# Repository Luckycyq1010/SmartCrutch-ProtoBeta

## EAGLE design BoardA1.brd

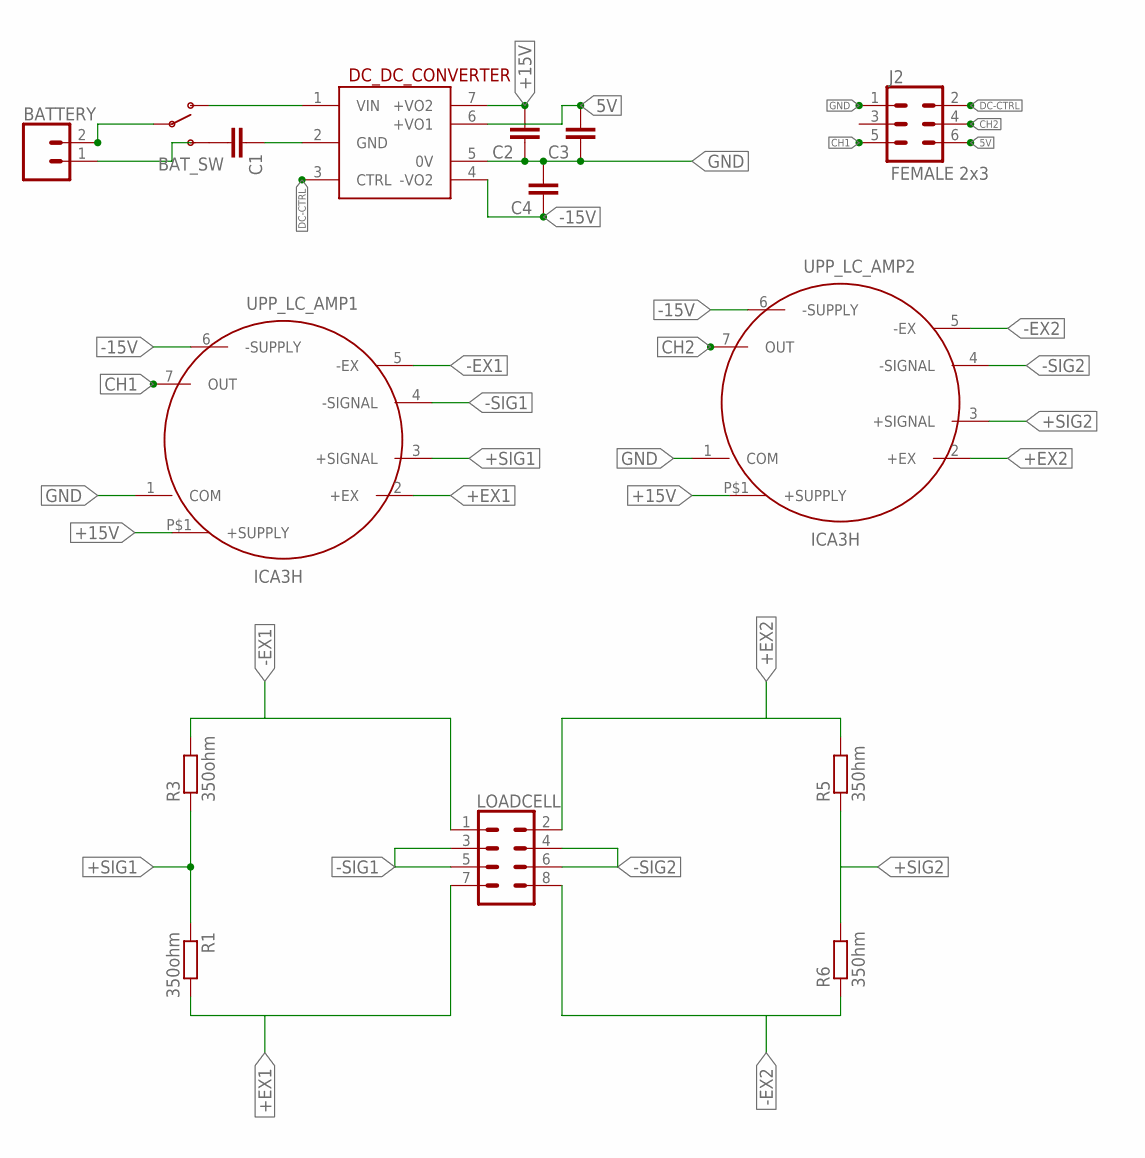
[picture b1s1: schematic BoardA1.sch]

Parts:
BATTERY: CONN_02; 1X02
BAT_SW: SWITCH-SPDTPTH; SWITCH-SPDT
C1, C2, C3, C4: C2.5/2; C2.5-2
DC_DC_CONVERTER: DC-DC; DC-DCCONVERTER
J2: FEMALE 2x3; 2X3
LOADCELL: CONN_04X2; 2X4
R1, R3: 350ohm; 0207/10
R5, R6: 350hm; 0207/10
UPP_LC_AMP1, UPP_LC_AMP2: ICA3H

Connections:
5V: C3.2, DC_DC_CONVERTER.6 (+VO1), J2.6
+15V: C2.2, DC_DC_CONVERTER.7 (+VO2), UPP_LC_AMP1.P$1 (+SUPPLY), UPP_LC_AMP2.P$1 (+SUPPLY)
+EX1: LOADCELL.7, R1.2, UPP_LC_AMP1.2 (+EX)
+EX2: LOADCELL.2, R5.2, UPP_LC_AMP2.2 (+EX)
+SIG1: R1.1, R3.1, UPP_LC_AMP1.3 (+SIGNAL)
+SIG2: R5.1, R6.2, UPP_LC_AMP2.3 (+SIGNAL)
-15V: C4.1, DC_DC_CONVERTER.4 (-VO2), UPP_LC_AMP1.6 (-SUPPLY), UPP_LC_AMP2.6 (-SUPPLY)
-EX1: LOADCELL.1, R3.2, UPP_LC_AMP1.5 (-EX)
-EX2: LOADCELL.8, R6.1, UPP_LC_AMP2.5 (-EX)
-SIG1: LOADCELL.3, LOADCELL.5, UPP_LC_AMP1.4 (-SIGNAL)
-SIG2: LOADCELL.4, LOADCELL.6, UPP_LC_AMP2.4 (-SIGNAL)
CH1: J2.5, UPP_LC_AMP1.7 (OUT)
CH2: J2.4, UPP_LC_AMP2.7 (OUT)
DC-CTRL: DC_DC_CONVERTER.3 (CTRL), J2.2
GND: C2.1, C3.1, C4.2, DC_DC_CONVERTER.5 (0V), J2.1, UPP_LC_AMP1.1 (COM), UPP_LC_AMP2.1 (COM)
unnamed: C1.1, DC_DC_CONVERTER.2 (GND)
unnamed: BAT_SW.1 (O), DC_DC_CONVERTER.1 (VIN)
unnamed: BATTERY.2, BAT_SW.2

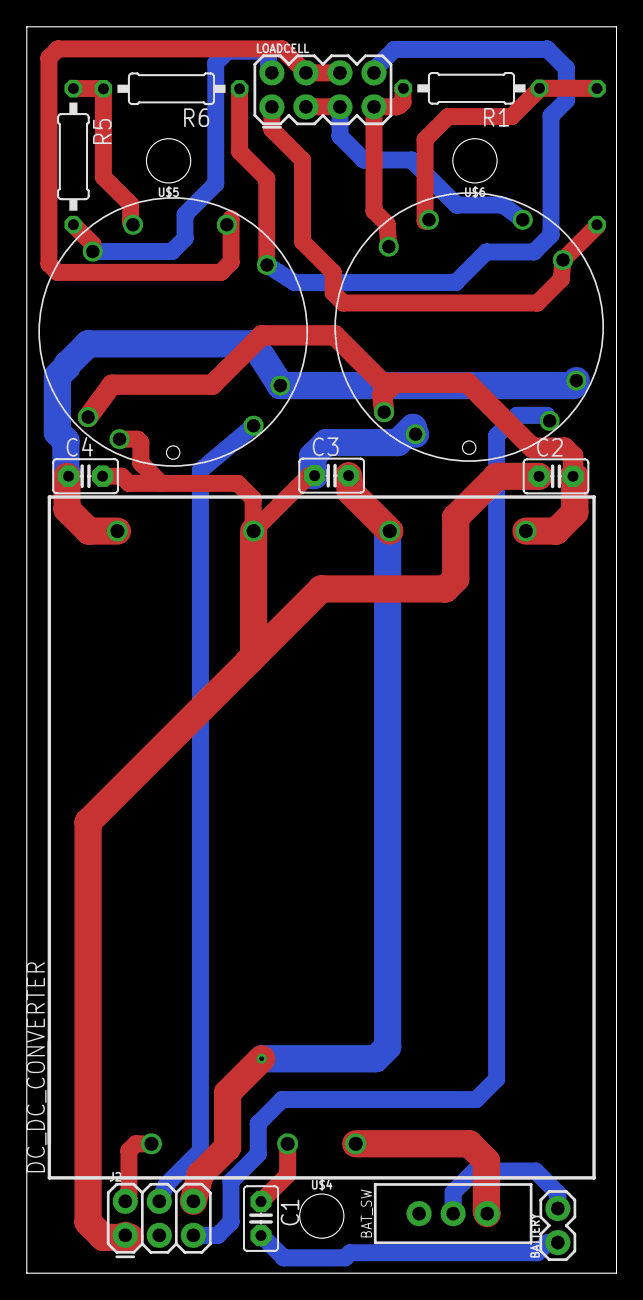
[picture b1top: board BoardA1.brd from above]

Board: 2 copper layers, 44.0 x 93.0 mm, 18 parts (1 on the bottom side), 18 nets.

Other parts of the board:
U$4, U$5, U$6: STAND-OFF

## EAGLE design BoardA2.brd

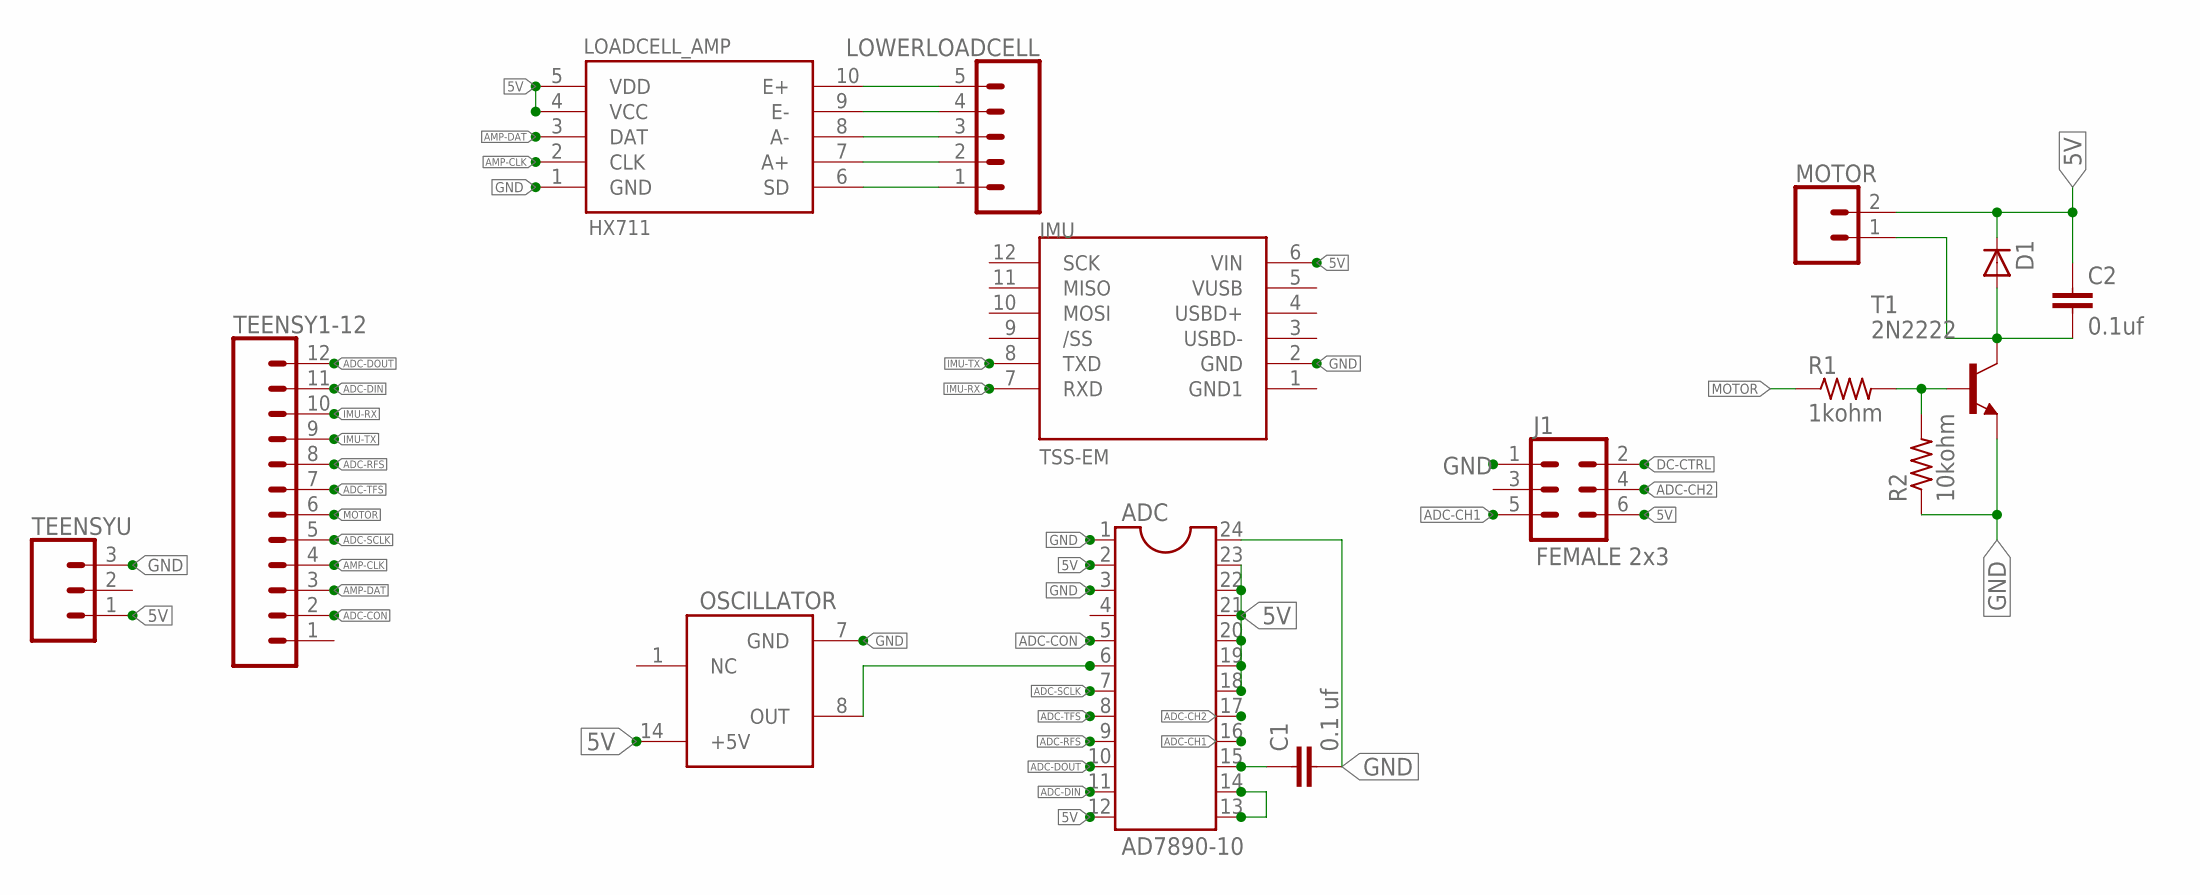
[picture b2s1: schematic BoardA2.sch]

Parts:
ADC: AD7890-10; DIL24-3
C1: 0.1 uf; C5B2.5
C2: 0.1uf; C5B2.5
D1: DIODE_E-DO35-7; DIODE_DO35-7
IMU: TSS-EM; IMU
J1: FEMALE 2x3; 2X3
LOADCELL_AMP: HX711; LOADCELLAMP2
LOWERLOADCELL: CONN_05; 1X05
MOTOR: CONN_02; 1X02
OSCILLATOR: CLOCK-ECS-100X; ECS-100X
R1: 1kohm; 0204/5
R2: 10kohm; 0204/5
T1: 2N2222; TO18
TEENSY1-12: CONN_12; 1X12
TEENSYU: CONN_03; 1X03

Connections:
5V: ADC.2, ADC.12, ADC.18, ADC.19, ADC.20, ADC.21, ADC.22, ADC.23, C2.1, D1.C (A), IMU.6 (VIN), J1.6, LOADCELL_AMP.4 (VCC), LOADCELL_AMP.5 (VDD), MOTOR.2, OSCILLATOR.14 (+5V), TEENSYU.1
ADC-CH1: ADC.16, J1.5
ADC-CH2: ADC.17, J1.4
ADC-CLK: ADC.6, OSCILLATOR.8 (OUT)
ADC-CON: ADC.5, TEENSY1-12.2
ADC-DIN: ADC.11, TEENSY1-12.11
ADC-DOUT: ADC.10, TEENSY1-12.12
ADC-RFS: ADC.9, TEENSY1-12.8
ADC-SCLK: ADC.7, TEENSY1-12.5
ADC-TFS: ADC.8, TEENSY1-12.7
AMP-A+: LOADCELL_AMP.7 (A+), LOWERLOADCELL.2
AMP-A-: LOADCELL_AMP.8 (A-), LOWERLOADCELL.3
AMP-CLK: LOADCELL_AMP.2 (CLK), TEENSY1-12.4
AMP-DAT: LOADCELL_AMP.3 (DAT), TEENSY1-12.3
AMP-E+: LOADCELL_AMP.10 (E+), LOWERLOADCELL.5
AMP-E-: LOADCELL_AMP.9 (E-), LOWERLOADCELL.4
AMP-SD: LOADCELL_AMP.6 (SD), LOWERLOADCELL.1
DC-CTRL: J1.2
GND: ADC.1, ADC.3, ADC.24, C1.2, IMU.2 (GND), J1.1, LOADCELL_AMP.1 (GND), OSCILLATOR.7 (GND), R2.1, T1.1 (E), TEENSYU.3
IMU-RX: IMU.7 (RXD), TEENSY1-12.10
IMU-TX: IMU.8 (TXD), TEENSY1-12.9
MOTOR: R1.1, TEENSY1-12.6
unnamed: ADC.13, ADC.14
unnamed: ADC.15, C1.1
unnamed: C2.2, D1.A (C), MOTOR.1, T1.3 (C)
unnamed: R1.2, R2.2, T1.2 (B)

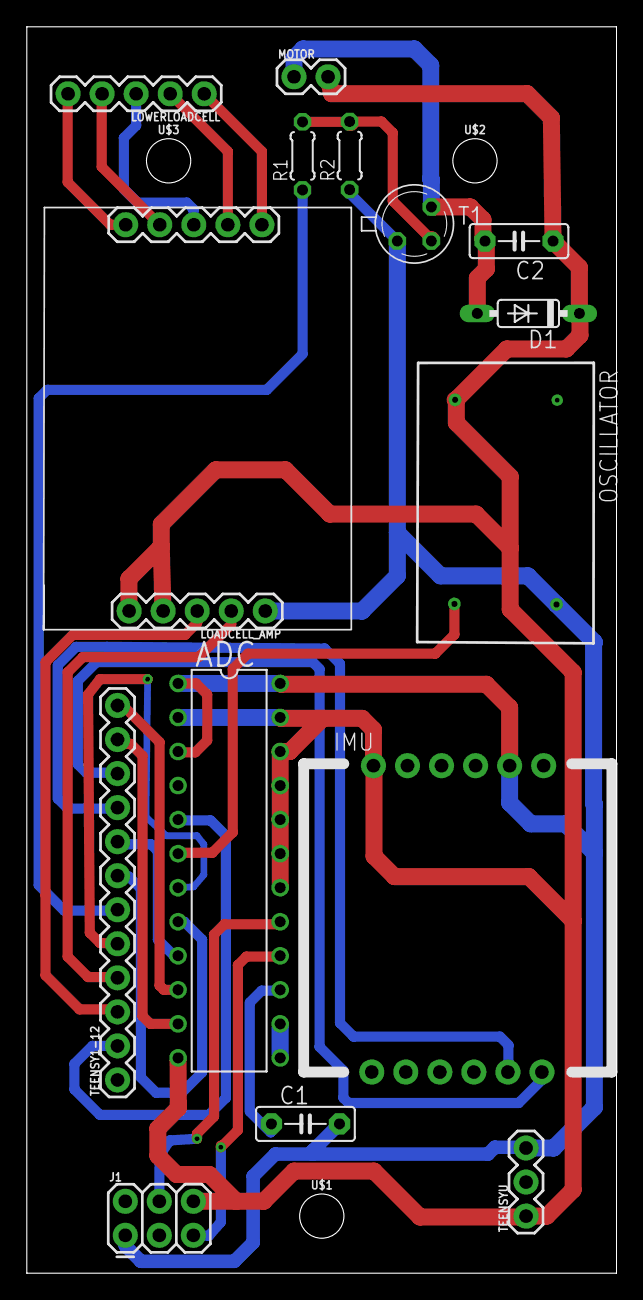
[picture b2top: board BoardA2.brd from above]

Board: 2 copper layers, 44.0 x 93.0 mm, 18 parts (0 on the bottom side), 25 nets.

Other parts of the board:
U$1, U$2, U$3: STAND-OFF

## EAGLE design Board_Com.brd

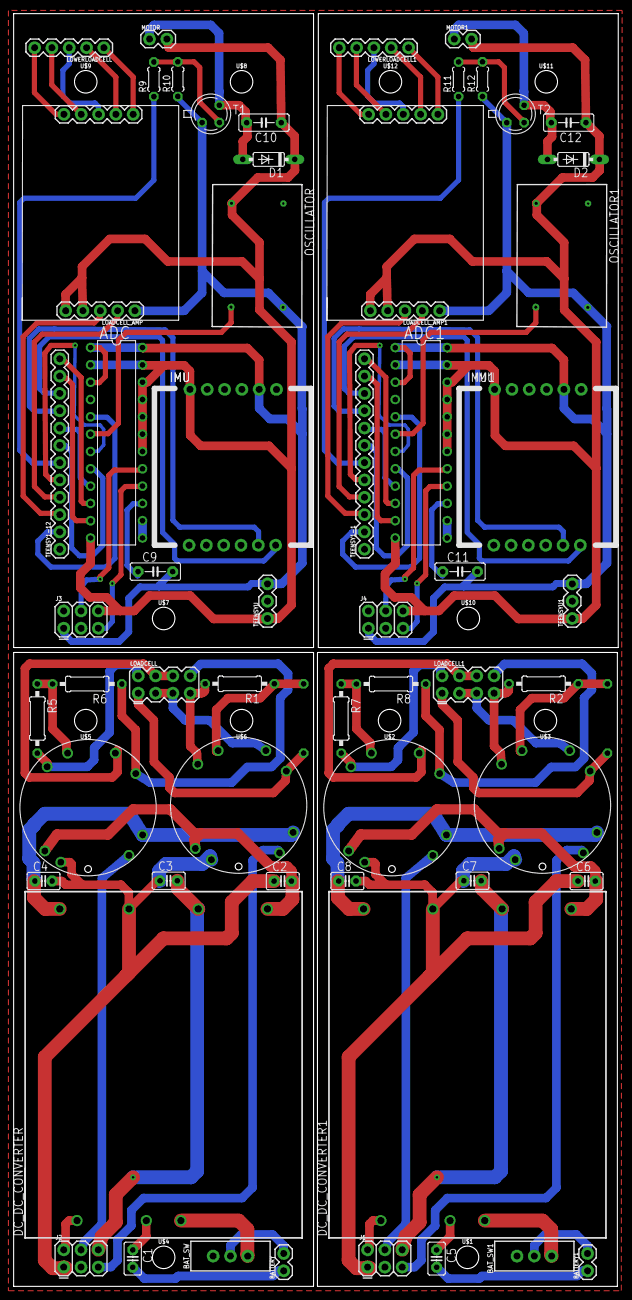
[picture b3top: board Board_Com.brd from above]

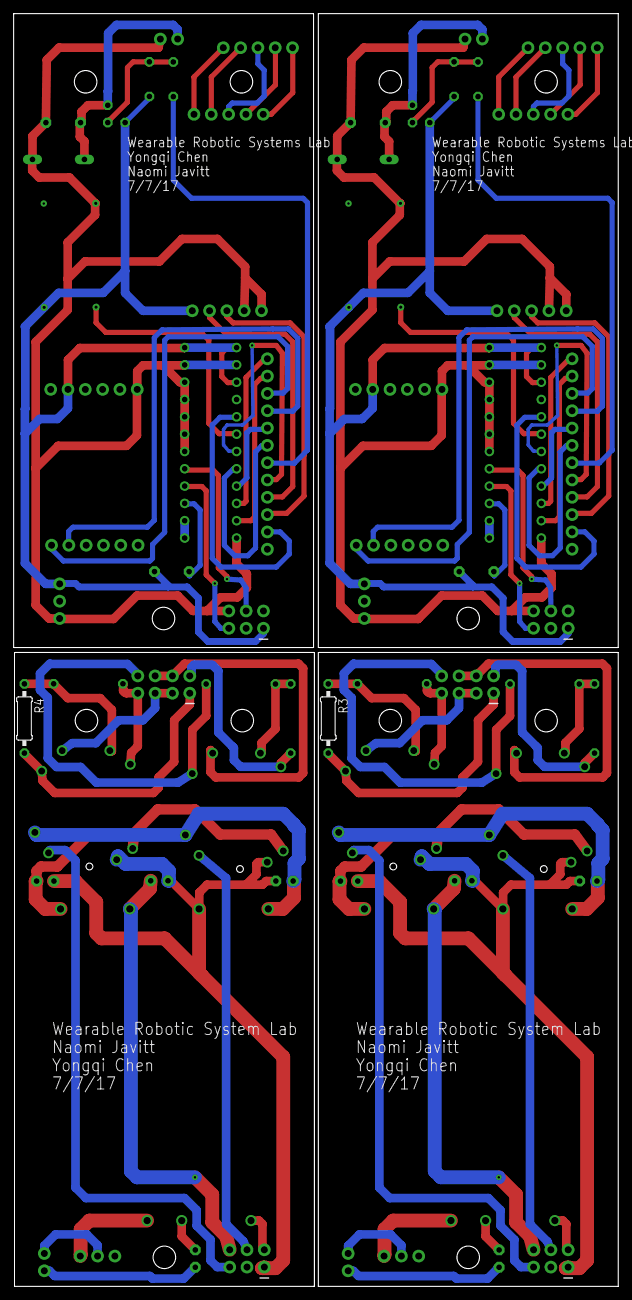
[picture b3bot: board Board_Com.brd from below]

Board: 2 copper layers, 88.7 x 186.7 mm, 72 parts (2 on the bottom side), 86 nets.

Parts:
ADC, ADC1: AD7890-10; DIL24-3
BATTERY, BATTERY1: 1X02
BAT_SW, BAT_SW1: SWITCH-SPDT
C1, C2, C3, C4, C5, C6, C7, C8: C2.5-2
C9, C11: 0.1 uf; C5B2.5
C10, C12: 0.1uf; C5B2.5
D1, D2: DIODE_DO35-7
DC_DC_CONVERTER, DC_DC_CONVERTER1: DC-DCCONVERTER
IMU, IMU1: TSS-EM; IMU
J1, J2, J3, J4: FEMALE 2x3; 2X3
LOADCELL, LOADCELL1: 2X4
LOADCELL_AMP, LOADCELL_AMP1: HX711; LOADCELLAMP2
LOWERLOADCELL, LOWERLOADCELL1: 1X05
MOTOR, MOTOR1: 1X02
OSCILLATOR, OSCILLATOR1: CLOCK-ECS-100X; ECS-100X
R1, R2, R3, R4: 350ohm; 0207/10
R5, R6, R7, R8: 350hm; 0207/10
R9, R11: 1kohm; 0204/5
R10, R12: 10kohm; 0204/5
T1, T2: 2N2222; TO18
TEENSY1-1, TEENSY1-12: 1X12
TEENSYU, TEENSYU1: 1X03
U$1, U$2, U$3, U$4, U$5, U$6, U$7, U$8, U$9, U$10, U$11, U$12: STAND-OFF
UPP_LC_AMP1, UPP_LC_AMP2, UPP_LC_AMP3, UPP_LC_AMP4: ICA3H

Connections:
5V: C3.2, DC_DC_CONVERTER.6, J2.6
5V1: C7.2, DC_DC_CONVERTER1.6, J1.6
5V2: ADC.2, ADC.12, ADC.18, ADC.19, ADC.20, ADC.21, ADC.22, ADC.23, C10.1, D1.C, IMU.6, J3.6, LOADCELL_AMP.4, LOADCELL_AMP.5, MOTOR.2, OSCILLATOR.14, TEENSYU.1
5V3: ADC1.2, ADC1.12, ADC1.18, ADC1.19, ADC1.20, ADC1.21, ADC1.22, ADC1.23, C12.1, D2.C, IMU1.6, J4.6, LOADCELL_AMP1.4, LOADCELL_AMP1.5, MOTOR1.2, OSCILLATOR1.14, TEENSYU1.1
+15V: C2.2, DC_DC_CONVERTER.7, UPP_LC_AMP1.P$1, UPP_LC_AMP2.P$1
+15V1: C6.2, DC_DC_CONVERTER1.7, UPP_LC_AMP3.P$1, UPP_LC_AMP4.P$1
+EX1: LOADCELL.7, R1.2, UPP_LC_AMP1.2
+EX2: LOADCELL.2, R5.2, UPP_LC_AMP2.2
+EX3: LOADCELL1.7, R2.2, UPP_LC_AMP3.2
+EX4: LOADCELL1.2, R7.2, UPP_LC_AMP4.2
+SIG1: R1.1, R3.1, UPP_LC_AMP1.3
+SIG2: R5.1, R6.2, UPP_LC_AMP2.3
+SIG3: R2.1, R4.1, UPP_LC_AMP3.3
+SIG4: R7.1, R8.2, UPP_LC_AMP4.3
-15V: C4.1, DC_DC_CONVERTER.4, UPP_LC_AMP1.6, UPP_LC_AMP2.6
-15V1: C8.1, DC_DC_CONVERTER1.4, UPP_LC_AMP3.6, UPP_LC_AMP4.6
-EX1: LOADCELL.1, R3.2, UPP_LC_AMP1.5
-EX2: LOADCELL.8, R6.1, UPP_LC_AMP2.5
-EX3: LOADCELL1.1, R4.2, UPP_LC_AMP3.5
-EX4: LOADCELL1.8, R8.1, UPP_LC_AMP4.5
-SIG1: LOADCELL.3, LOADCELL.5, UPP_LC_AMP1.4
-SIG2: LOADCELL.4, LOADCELL.6, UPP_LC_AMP2.4
-SIG3: LOADCELL1.3, LOADCELL1.5, UPP_LC_AMP3.4
-SIG4: LOADCELL1.4, LOADCELL1.6, UPP_LC_AMP4.4
ADC-CH1: ADC.16, J3.5
ADC-CH2: ADC.17, J3.4
ADC-CH3: ADC1.16, J4.5
ADC-CH4: ADC1.17, J4.4
ADC-CLK: ADC.6, OSCILLATOR.8
ADC-CLK1: ADC1.6, OSCILLATOR1.8
ADC-CON: ADC.5, TEENSY1-12.2
ADC-CON1: ADC1.5, TEENSY1-1.2
ADC-DIN: ADC.11, TEENSY1-12.11
ADC-DIN1: ADC1.11, TEENSY1-1.11
ADC-DOUT: ADC.10, TEENSY1-12.12
ADC-DOUT1: ADC1.10, TEENSY1-1.12
ADC-RFS: ADC.9, TEENSY1-12.8
ADC-RFS1: ADC1.9, TEENSY1-1.8
ADC-SCLK: ADC.7, TEENSY1-12.5
ADC-SCLK1: ADC1.7, TEENSY1-1.5
ADC-TFS: ADC.8, TEENSY1-12.7
ADC-TFS1: ADC1.8, TEENSY1-1.7
AMP-A+: LOADCELL_AMP.7, LOWERLOADCELL.2
AMP-A+1: LOADCELL_AMP1.7, LOWERLOADCELL1.2
AMP-A-: LOADCELL_AMP.8, LOWERLOADCELL.3
AMP-A-1: LOADCELL_AMP1.8, LOWERLOADCELL1.3
AMP-CLK: LOADCELL_AMP.2, TEENSY1-12.4
AMP-CLK1: LOADCELL_AMP1.2, TEENSY1-1.4
AMP-DAT: LOADCELL_AMP.3, TEENSY1-12.3
AMP-DAT1: LOADCELL_AMP1.3, TEENSY1-1.3
AMP-E+: LOADCELL_AMP.10, LOWERLOADCELL.5
AMP-E+1: LOADCELL_AMP1.10, LOWERLOADCELL1.5
AMP-E-: LOADCELL_AMP.9, LOWERLOADCELL.4
AMP-E-1: LOADCELL_AMP1.9, LOWERLOADCELL1.4
AMP-SD: LOADCELL_AMP.6, LOWERLOADCELL.1
AMP-SD1: LOADCELL_AMP1.6, LOWERLOADCELL1.1
CH1: J2.5, UPP_LC_AMP1.7
CH2: J2.4, UPP_LC_AMP2.7
CH3: J1.5, UPP_LC_AMP3.7
CH4: J1.4, UPP_LC_AMP4.7
DC-CTRL: DC_DC_CONVERTER.3, J2.2
DC-CTRL1: DC_DC_CONVERTER1.3, J1.2
GND: C2.1, C3.1, C4.2, DC_DC_CONVERTER.5, J2.1, UPP_LC_AMP1.1, UPP_LC_AMP2.1
GND1: C6.1, C7.1, C8.2, DC_DC_CONVERTER1.5, J1.1, UPP_LC_AMP3.1, UPP_LC_AMP4.1
GND2: ADC.1, ADC.3, ADC.24, C9.2, IMU.2, J3.1, LOADCELL_AMP.1, OSCILLATOR.7, R10.1, T1.1, TEENSYU.3
GND3: ADC1.1, ADC1.3, ADC1.24, C11.2, IMU1.2, J4.1, LOADCELL_AMP1.1, OSCILLATOR1.7, R12.1, T2.1, TEENSYU1.3
IMU-RX: IMU.7, TEENSY1-12.10
IMU-RX1: IMU1.7, TEENSY1-1.10
IMU-TX: IMU.8, TEENSY1-12.9
IMU-TX1: IMU1.8, TEENSY1-1.9
MOTOR: R9.1, TEENSY1-12.6
MOTOR1: R11.1, TEENSY1-1.6
unnamed: C1.1, DC_DC_CONVERTER.2
unnamed: BAT_SW.1, DC_DC_CONVERTER.1
unnamed: C5.1, DC_DC_CONVERTER1.2
unnamed: BATTERY.2, BAT_SW.2
unnamed: BAT_SW1.1, DC_DC_CONVERTER1.1
unnamed: BATTERY1.2, BAT_SW1.2
unnamed: ADC.13, ADC.14
unnamed: ADC.15, C9.1
unnamed: C10.2, D1.A, MOTOR.1, T1.3
unnamed: R9.2, R10.2, T1.2
unnamed: ADC1.13, ADC1.14
unnamed: ADC1.15, C11.1
unnamed: C12.2, D2.A, MOTOR1.1, T2.3
unnamed: R11.2, R12.2, T2.2

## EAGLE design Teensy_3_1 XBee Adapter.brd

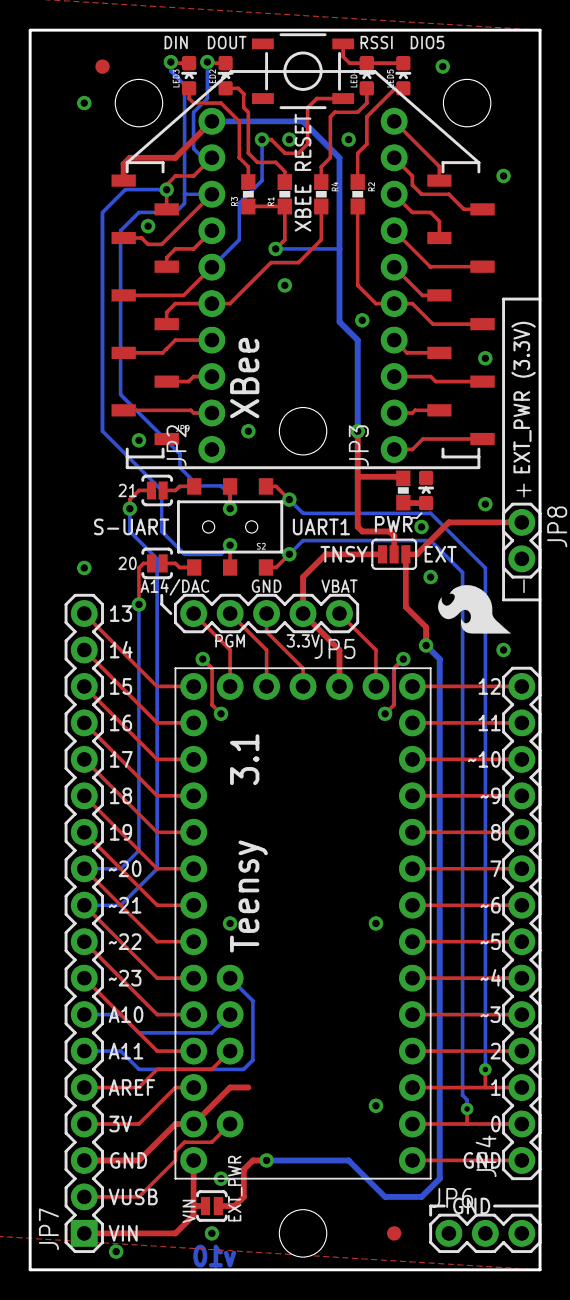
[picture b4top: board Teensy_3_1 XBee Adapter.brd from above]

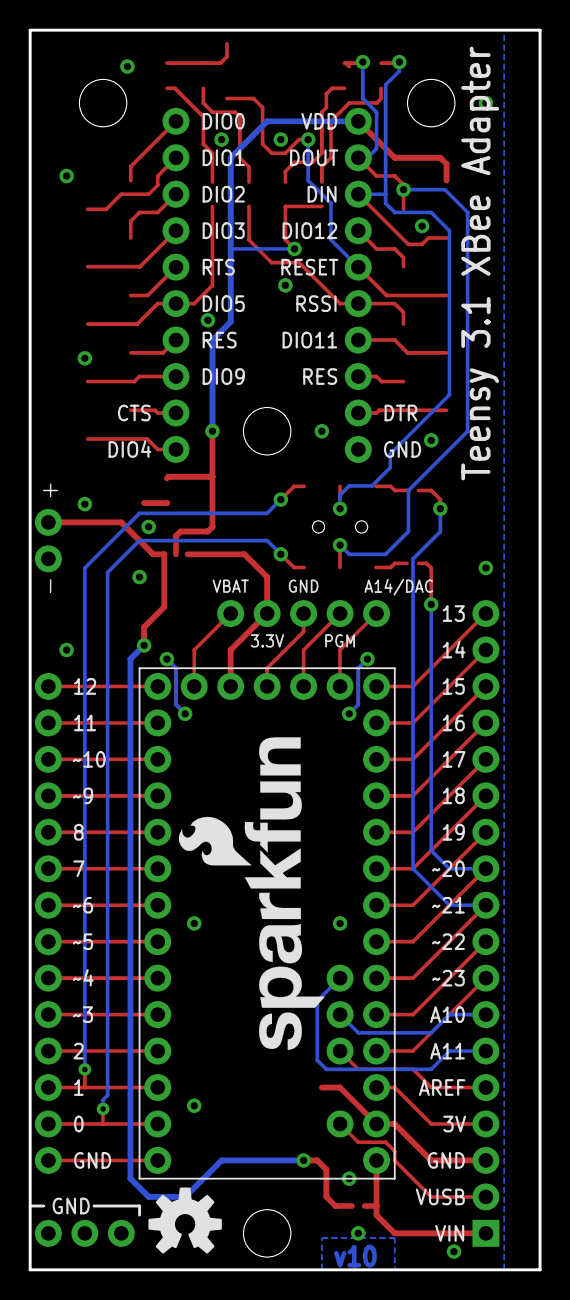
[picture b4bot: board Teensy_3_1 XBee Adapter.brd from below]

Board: 2 copper layers, 35.5 x 86.4 mm, 35 parts (2 on the bottom side), 62 nets.

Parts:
FID1, FID2: FIDUCIAL1X2; FIDUCIAL-1X2
FRAME1: CREATIVE_COMMONS
JP1: TEENSY-3.1NOSILK; TEENSY-3.1_NOSILK
JP2, JP3: 1X10_NO_SILK
JP4: DNP; 1X14
JP5: DNP; 1X05
JP6: DNP; 1X03
JP7: DNP\; 1X18
JP8: DNP; 1X02
JP9: CONN-09042; XBEE-SMD
LED1, LED2: Red; LED-0603
LED3, LED4, LED5: Green; LED-0603
LOGO1: SFE_LOGO_FLAME.2_INCH; SFE_LOGO_FLAME_.2
LOGO2: OSHW-LOGOM; OSHW-LOGO-M
LOGO3: SFE_LOGO_NAME_FLAME.2_INCH; SFE_LOGO_NAME_FLAME_.2
R1, R2, R3, R4, R11: 1k; 0603-RES
S2: DPDT; AYZ0202
S3: Reset; TACTILE-SWITCH-SMD
SJ1: D_TX; PAD-JUMPER-2-NC_BY_PASTE_YES_SILK
SJ3: D_RX; PAD-JUMPER-2-NC_BY_PASTE_YES_SILK
SJ4: JUMPER-PAD-3-2OF3_NC_BY_PASTE; PAD-JUMPER-3-2OF3_NC_BY_PASTE_YES_SILK_FULL_BOX
SJ5: EXT_JPR; PAD-JUMPER-2-NO_YES_SILK
STANDOFF1, STANDOFF2, STANDOFF3, STANDOFF4: STAND-OFF

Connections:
2: JP1.2, JP4.4
3: JP1.3, JP4.5
3.3V: JP1.3.3V, JP5.2, SJ4.3
3V: JP1.3V, JP7.4
4: JP1.4, JP4.6
5: JP1.5, JP4.7
6: JP1.6, JP4.8
7/RX3: JP1.7, JP4.9
8/TX3: JP1.8, JP4.10
9/RX2: JP1.9, JP4.11
10/TX2/CS: JP1.10, JP4.12
11/DOUT: JP1.11, JP4.13
12/DIN: JP1.12, JP4.14
13/SCK: JP1.13, JP7.18
A0/14: JP1.14, JP7.17
A1/15: JP1.15, JP7.16
A2/16: JP1.16, JP7.15
A3/17: JP1.17, JP7.14
A4/18/SDA0: JP1.18, JP7.13
A5/19/SCL0: JP1.19, JP7.12
A6/20: JP1.20, JP7.11, SJ3.1
A7/21: JP1.21, JP7.10, SJ1.1
A8/22: JP1.22, JP7.9
A9/23: JP1.23, JP7.8
A10: JP1.A10, JP7.7
A11: JP1.A11, JP7.6
A14/DAC: JP1.A14/DAC, JP5.5
AREF: JP1.AREF, JP7.5
CTS: JP3.2, JP9.12
DIO0: JP3.10, JP9.20
DIO1: JP3.9, JP9.19
DIO2: JP3.8, JP9.18
DIO3: JP3.7, JP9.17
DIO4: JP3.1, JP9.11
DIO5: JP3.5, JP9.15, R2.2
DIO9: JP3.3, JP9.13
DIO11: JP2.4, JP9.7
DIO12: JP2.7, JP9.4
DTR: JP2.2, JP9.9
EXT_3.3V: JP8.1, SJ4.1, SJ5.2
GND: JP1.AGND, JP1.GND, JP1.GND1, JP2.1, JP4.1, JP5.3, JP6.1, JP6.2, JP6.3, JP7.3, JP8.2, JP9.10, LED1.C, LED4.C, LED5.C, S3.3
IN: JP2.8, JP9.3, LED3.C, S2.5
unnamed: LED1.A, R11.1
unnamed: LED2.A, R1.2
unnamed: LED3.A, R3.2
unnamed: LED4.A, R4.1
unnamed: LED5.A, R2.1
unnamed: S2.6, SJ1.2
unnamed: S2.3, SJ3.2
OUT: JP2.9, JP9.2, LED2.C, S2.2
PROG: JP1.PROG, JP5.4
RES: JP2.3, JP9.8
RES2: JP3.4, JP9.14
RESET: JP2.6, JP9.5, S3.1
RSSI: JP2.5, JP9.6, R4.2
RTS: JP3.6, JP9.16
UART_RX: JP1.0, JP4.2, S2.1
UART_TX: JP1.1, JP4.3, S2.4
VBAT: JP1.VBAT, JP5.1
VIN: JP1.VIN, JP7.1, SJ5.1
VUSB: JP1.VUSB, JP7.2
XBEE_VDD: JP2.10, JP9.1, R1.1, R3.1, R11.2, SJ4.2

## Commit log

2017-06-15 SmartCrutch
2017-06-15 LIbrary
2017-06-15 test
    test
2017-06-16 Starting Routing Board
2017-06-19 routed Top Layer Board
2017-06-19 updated
    added holes to attach boards
2017-06-20 fixed library
2017-06-20 changed IMU to through hole
2017-06-20 Schematic update on the middle Board
2017-06-21 Updated both Boards
    - Added holes
    - Changed connectors
    - routed both Boards
2017-06-21 Routing Update
2017-06-22 Routing and connection update
2017-06-22 Updated
    Fixed Hole placment,connectors, routing issues
2017-06-22 Motor Components
2017-06-22 Fix error
2017-06-22 hot fix2
2017-06-22 hotfix3
2017-06-22 connector 04x2 on Power board
2017-06-22 update-moved capacitor
2017-06-22 motor component2
2017-06-24 Motor update corrected
2017-06-24 Motor and pin update 2
2017-06-26 routed middle board
2017-06-26 made wire and vias thicker
2017-06-26 push
2017-06-26 added connector
2017-06-26 update2
2017-06-26 update 3
    added battery connector
2017-06-26 moved motor connector
2017-06-26 Teensy Pin Update 1
2017-06-26 moved connetors
2017-06-27 Teensy Pin Update2
2017-06-27 Resolve Conflict 1
2017-06-27 save history
2017-06-27 fixed Conflict
2017-06-27 fixed conflict2
2017-06-27 Rerouted Board 2
2017-06-27 printed Dxf of Board2
2017-06-28 dxf files
2017-06-28 adjusted components
2017-06-29 connect motor
2017-06-29 Connections on Power board
    - hook up the load cell connectors
    - ch1 and ch2 connection to the middle board
2017-06-29 Routing1
2017-06-29 solve conflit
2017-06-29 conflict resolve2
2017-06-29 conflit
2017-06-29 moved connector board 1
2017-07-02 Resolve Conflit & add a Teensy Pin
2017-07-02 Routing the power board
    Work in progress
2017-07-05 Rerouting 1
    Please do not push now. Thanks
2017-07-05 Update 2
2017-07-05 update 2b
2017-07-06 Mid board Rerouting 1
    Work in progress. Please do not commit any changes to Board2
2017-07-06 Changed Power connector
2017-07-06 rerouting 2
2017-07-06 update3
2017-07-06 Board2 Missing signal
2017-07-06 wire missing connection
2017-07-06 minor trace changes
2017-07-07 changed loadcell size
2017-07-07 updated library
2017-07-07 minor b1 changes
2017-07-07 update library and silkscreen
2017-07-07 rerouting
2017-07-07 changed resistor size
2017-07-07 routing
2017-07-07 final changes
2017-07-07 last update
2017-07-07 cosmetic changes

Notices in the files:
parts and their libraries:
SparkFun-Electromechanical: Licensing: Creative Commons ShareAlike 4.0 International - https://creativecommons.org/licenses/by-sa/4.0
SparkFun-Aesthetics: Released under the Creative Commons Attribution Share-Alike 4.0 License
SparkFun-Aesthetics: https://creativecommons.org/licenses/by-sa/4.0
